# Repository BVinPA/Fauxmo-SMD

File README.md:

# Fauxmo-SMD
Surface mount version of the Fauxmo controller board.  Includes Eagle files for the schematic and board, along with STLs for an enclosure.  There are two options for the bottom - a solid one, or one with a hole if you are using a right-angle programming header. The full project is here: https://www.electroschematics.com/home-iot-voice-controlled-lab-lights-amazon-alexa-esp8266/

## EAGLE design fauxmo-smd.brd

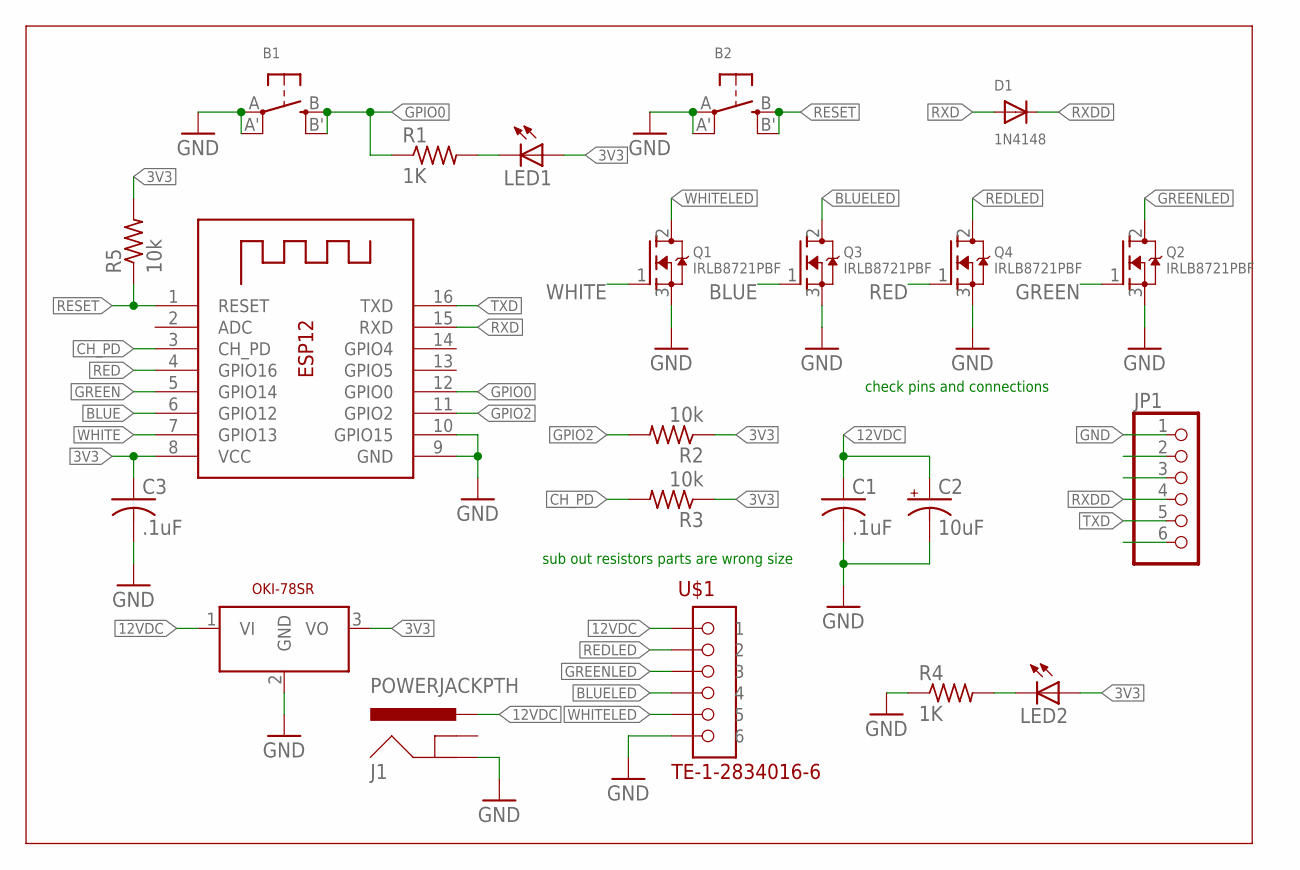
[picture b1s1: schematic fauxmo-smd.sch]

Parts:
B1, B2: SWITCH_TACT_SMT; EVQ-Q2
C1, C3: .1uF; C0805
C2: 10uF; E2,5-5
D1: 1N4148; SOD-123
J1: POWERJACKPTH; BARREL-2.1
JP1: PINHD-1X6; 1X06
LED1, LED2: LEDCHIP-LED0805; CHIP-LED0805
OKI: DCDC_OKI-78SROKI-78SRV; OKI-78SRH
Q1, Q2, Q3, Q4: IRLB8721PBF; TO220V
R1, R4: 1K; R0805
R2, R3, R5: 10k; R0805
U$1: TE-1-2834016-6
X1: ESP-12

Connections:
3V3: C3.1, LED1.A, LED2.A, OKI.3 (VO), R2.1, R3.1, R5.2, X1.8 (VCC)
12VDC: C1.1, C2.+, J1.PWR, OKI.1 (VI), U$1.P$6 (1)
BLUE: Q3.1 (G), X1.6 (GPIO12)
BLUELED: Q3.2 (D), U$1.P$3 (4)
CH_PD: R3.2, X1.3 (CH_PD)
GND: B1.A, B1.A' (P1), B2.A, B2.A' (P1), C1.2, C2.-, C3.2, J1.GND, JP1.1, OKI.2 (GND), Q1.3 (S), Q2.3 (S), Q3.3 (S), Q4.3 (S), R4.1, U$1.P$1 (6), X1.9 (GND), X1.10 (GPIO15)
GPIO0: B1.B (S), B1.B' (S1), R1.1, X1.12 (GPIO0)
GPIO2: R2.2, X1.11 (GPIO2)
GREEN: Q2.1 (G), X1.5 (GPIO14)
GREENLED: Q2.2 (D), U$1.P$4 (3)
unnamed: LED1.C, R1.2
unnamed: LED2.C, R4.2
RED: Q4.1 (G), X1.4 (GPIO16)
REDLED: Q4.2 (D), U$1.P$5 (2)
RESET: B2.B (S), B2.B' (S1), R5.1, X1.1 (RESET)
RXD: D1.A, X1.15 (RXD)
RXDD: D1.C, JP1.4
TXD: JP1.5, X1.16 (TXD)
WHITE: Q1.1 (G), X1.7 (GPIO13)
WHITELED: Q1.2 (D), U$1.P$2 (5)

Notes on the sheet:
OKI-78SR
sub out resistors parts are wrong size
check pins and connections

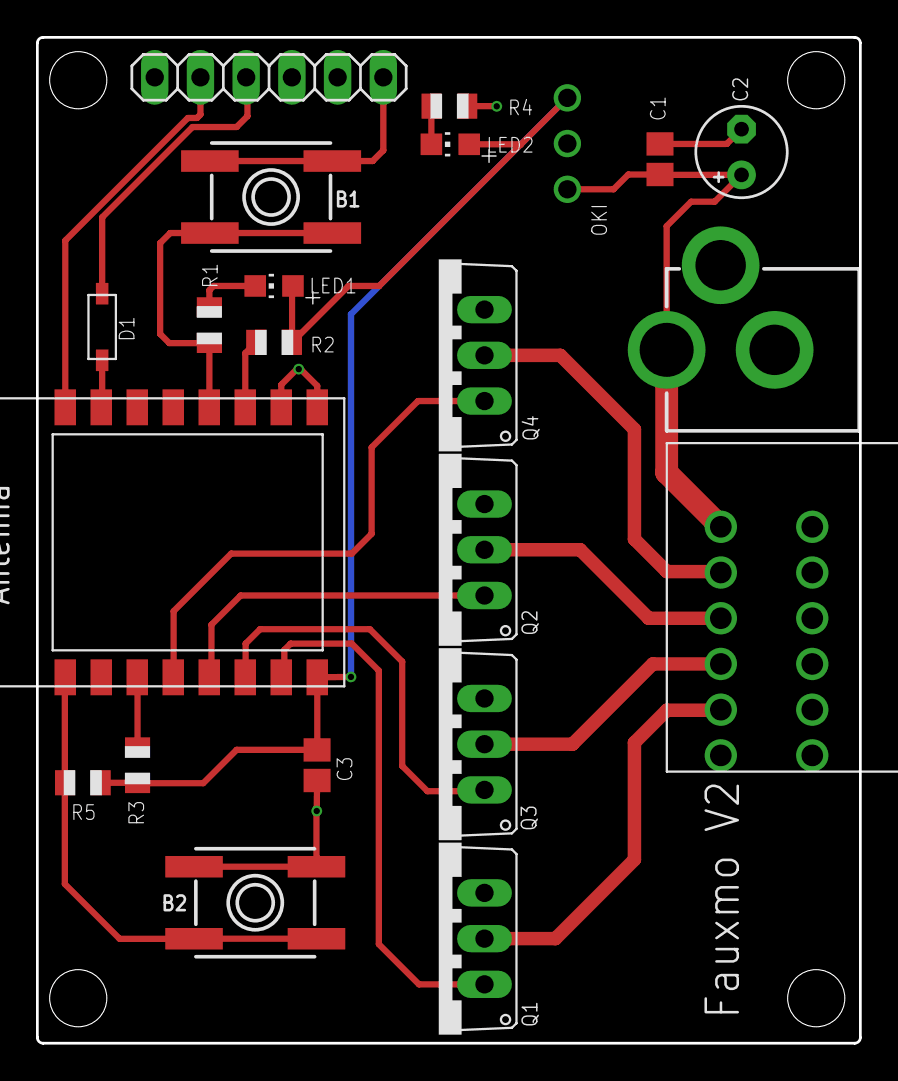
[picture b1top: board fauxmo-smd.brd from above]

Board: 2 copper layers, 45.7 x 55.9 mm, 23 parts (1 on the bottom side), 20 nets.

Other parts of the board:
U$2: OSHW_5MM

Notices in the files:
parts and their libraries:
microbuilder: This work is placed in the public domain, and may be freely used for commercial and non-commercial work with the following conditions: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
